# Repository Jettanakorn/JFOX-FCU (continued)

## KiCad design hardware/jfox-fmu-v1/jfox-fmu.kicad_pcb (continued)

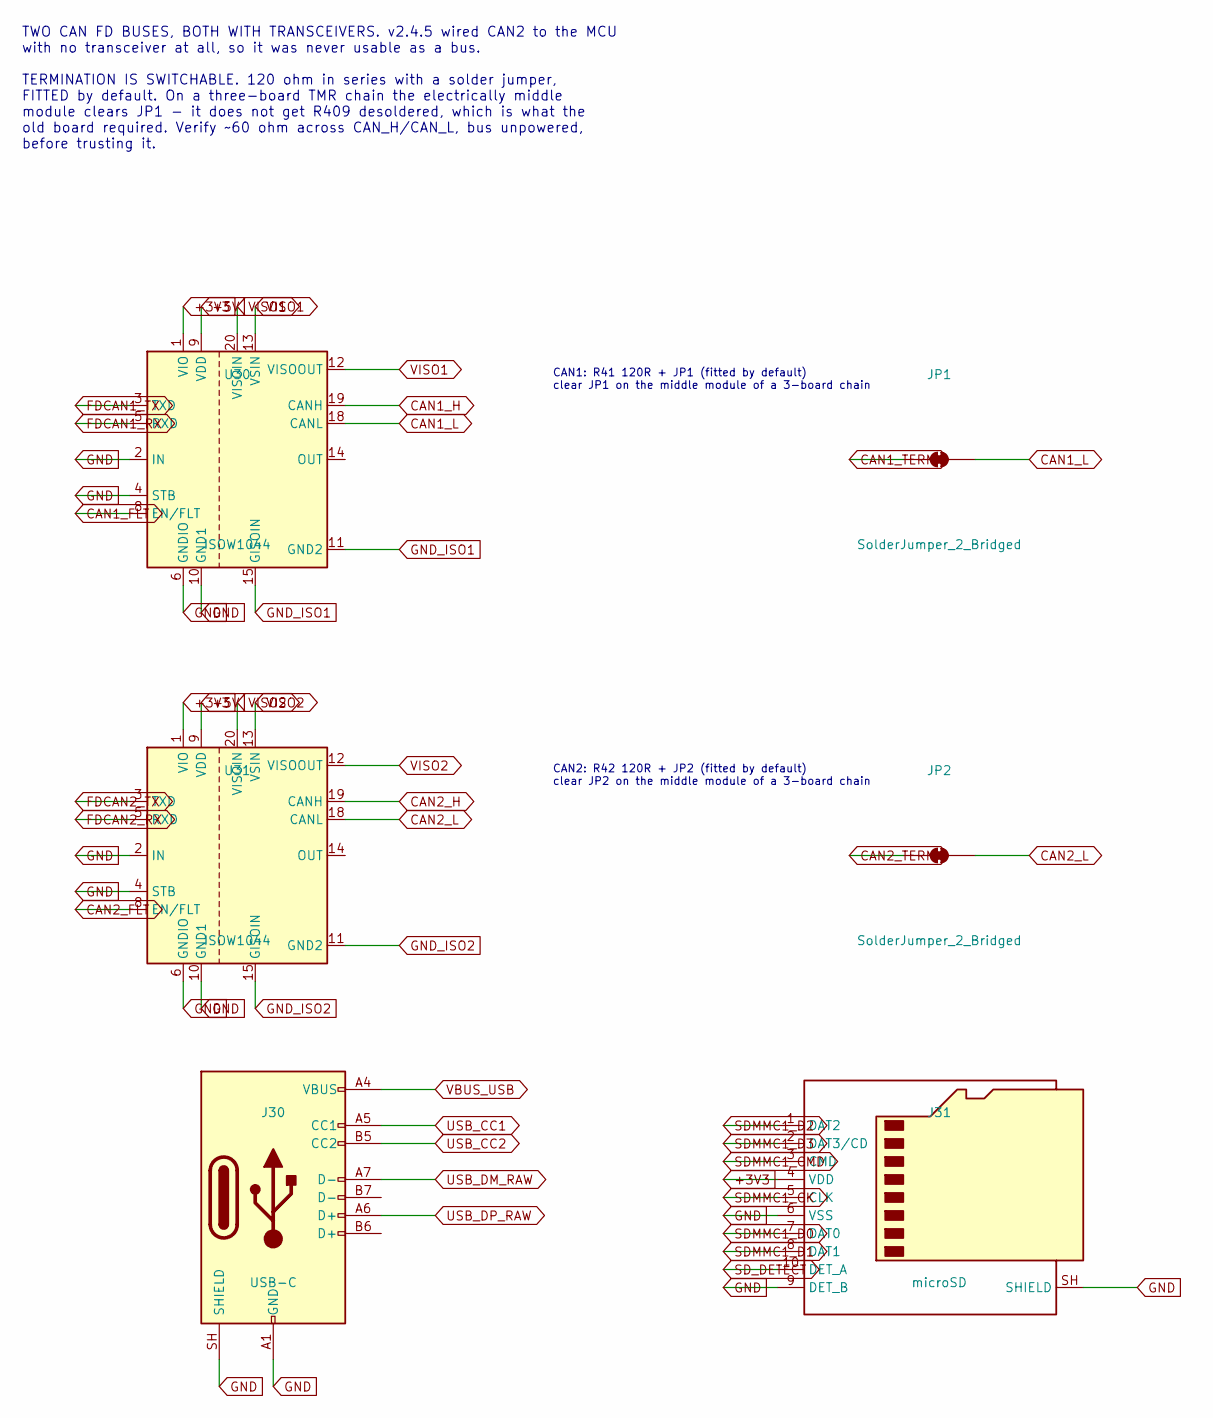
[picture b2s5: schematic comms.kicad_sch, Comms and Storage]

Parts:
J30: USB-C; USB_C_Receptacle_GCT_USB4085
J31: microSD; microSD_HC_Hirose_DM3AT-SF-PEJM5
JP1, JP2: SolderJumper_2_Bridged; SolderJumper-2_P1.3mm_Bridged_Pad1.0x1.5mm
U30, U31: ISOW1044; SOIC-20W_7.5x12.8mm_P1.27mm

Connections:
+3V3: J31.4 (VDD), U30.1 (VIO), U31.1 (VIO); also elsewhere on the board
+5V: U30.9 (VDD), U31.9 (VDD); also elsewhere on the board
CAN1_FLT: U30.8 (EN/FLT); also elsewhere on the board
CAN1_H: U30.19 (CANH); also elsewhere on the board
CAN1_L: JP1.2 (B), U30.18 (CANL); also elsewhere on the board
CAN1_TERM: JP1.1 (A); also elsewhere on the board
CAN2_FLT: U31.8 (EN/FLT); also elsewhere on the board
CAN2_H: U31.19 (CANH); also elsewhere on the board
CAN2_L: JP2.2 (B), U31.18 (CANL); also elsewhere on the board
CAN2_TERM: JP2.1 (A); also elsewhere on the board
FDCAN1_RX: U30.5 (RXD); also elsewhere on the board
FDCAN1_TX: U30.3 (TXD); also elsewhere on the board
FDCAN2_RX: U31.5 (RXD); also elsewhere on the board
FDCAN2_TX: U31.3 (TXD); also elsewhere on the board
GND: J30.A1 (GND), J30.A12 (GND), J30.B1 (GND), J30.B12 (GND), J30.SH (SHIELD), J31.6 (VSS), J31.9 (DET_B), J31.SH (SHIELD), U30.2 (IN), U30.4 (STB), U30.6 (GNDIO), U30.10 (GND1), U31.2 (IN), U31.4 (STB), U31.6 (GNDIO), U31.10 (GND1); also elsewhere on the board
GND_ISO1: U30.11 (GND2), U30.15 (GISOIN), U30.16 (GISOIN), U30.17 (GISOIN); also elsewhere on the board
GND_ISO2: U31.11 (GND2), U31.15 (GISOIN), U31.16 (GISOIN), U31.17 (GISOIN); also elsewhere on the board
SDMMC1_CK: J31.5 (CLK); also elsewhere on the board
SDMMC1_CMD: J31.3 (CMD); also elsewhere on the board
SDMMC1_D0: J31.7 (DAT0); also elsewhere on the board
SDMMC1_D1: J31.8 (DAT1); also elsewhere on the board
SDMMC1_D2: J31.1 (DAT2); also elsewhere on the board
SDMMC1_D3: J31.2 (DAT3/CD); also elsewhere on the board
SD_DETECT: J31.10 (DET_A); also elsewhere on the board
USB_CC1: J30.A5 (CC1); also elsewhere on the board
USB_CC2: J30.B5 (CC2); also elsewhere on the board
USB_DM_RAW: J30.A7 (D-); also elsewhere on the board
USB_DP_RAW: J30.A6 (D+); also elsewhere on the board
VBUS_USB: J30.A4 (VBUS), J30.A9 (VBUS), J30.B4 (VBUS), J30.B9 (VBUS); also elsewhere on the board
VISO1: U30.12 (VISOOUT), U30.13 (VSIN), U30.20 (VISOIN); also elsewhere on the board
VISO2: U31.12 (VISOOUT), U31.13 (VSIN), U31.20 (VISOIN); also elsewhere on the board

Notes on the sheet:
TWO CAN FD BUSES, BOTH WITH TRANSCEIVERS. v2.4.5 wired CAN2 to the MCU with no transceiver at all, so it was never usable as a bus. TERMINATION IS SWITCHABLE. 120 ohm in series with a solder jumper, FITTED by default. On a three-board TMR chain the electrically middle module clears JP1 - it does no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
CAN1: R41 120R + JP1 (fitted by default) clear JP1 on the middle module of a 3-board chain
CAN2: R42 120R + JP2 (fitted by default) clear JP2 on the middle module of a 3-board chain

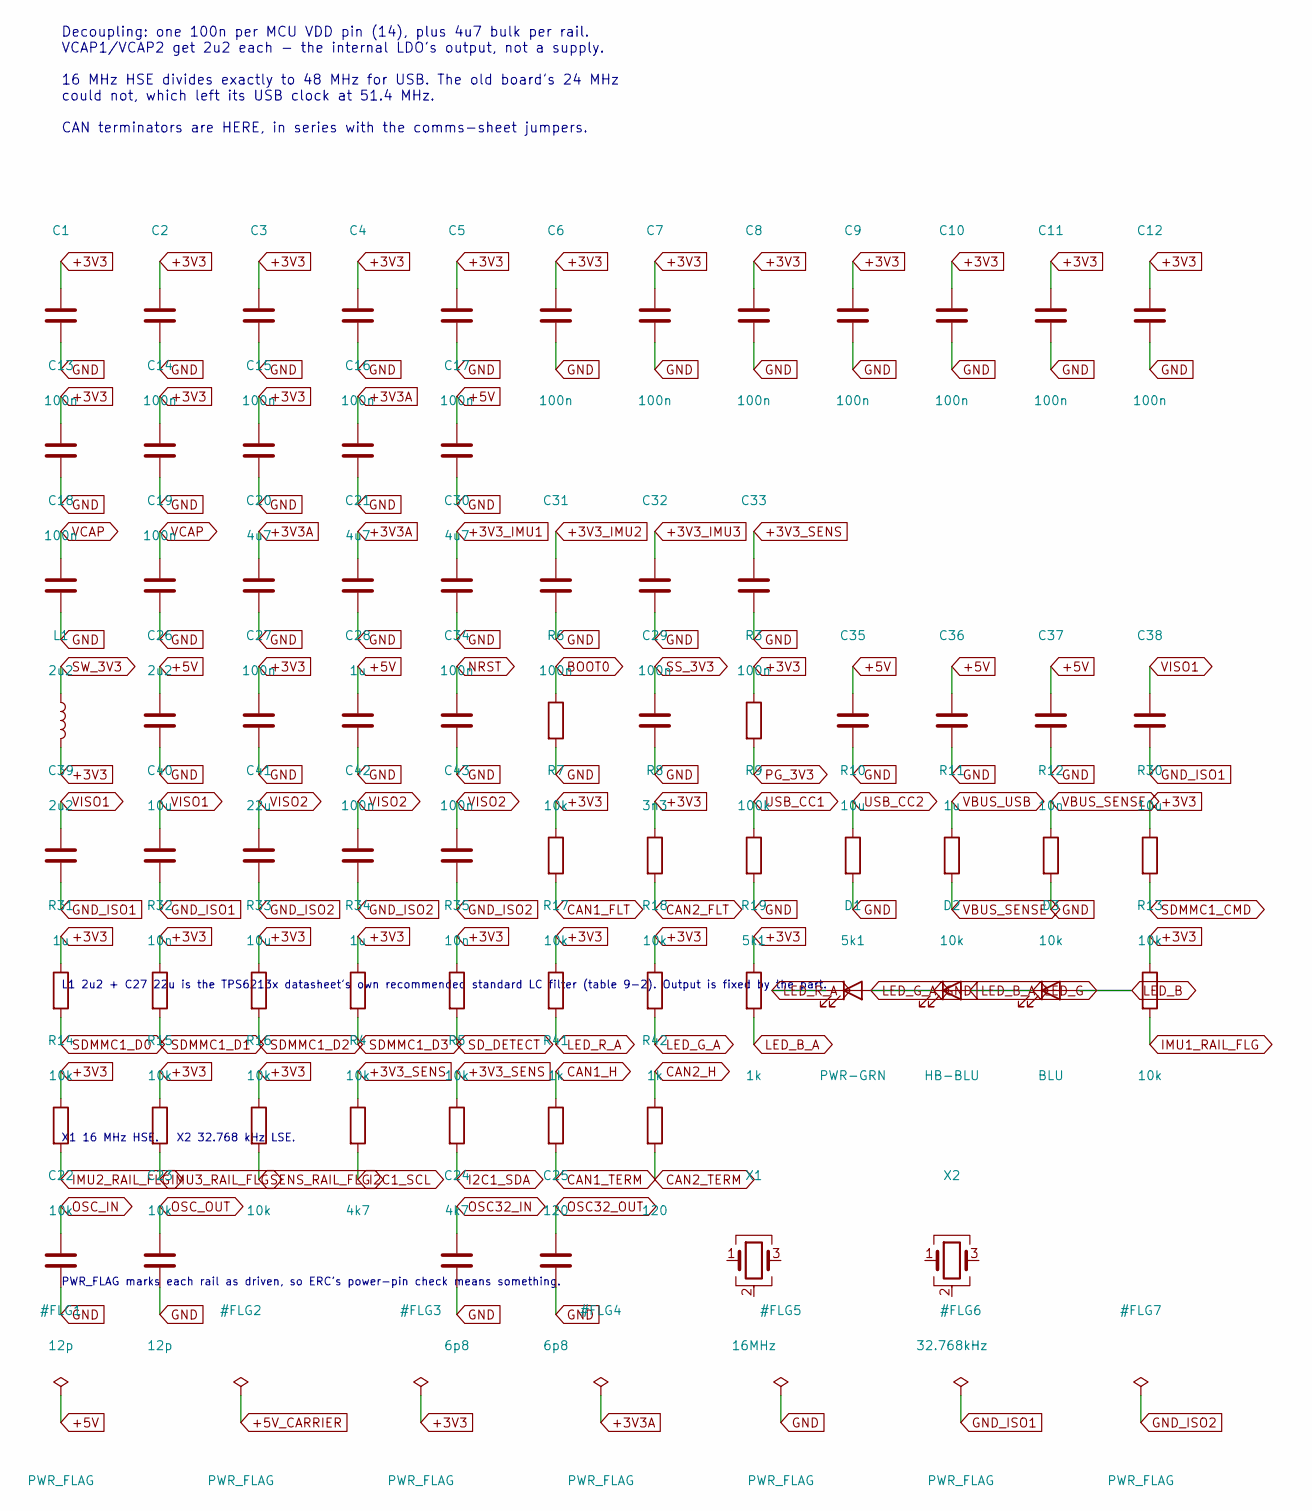
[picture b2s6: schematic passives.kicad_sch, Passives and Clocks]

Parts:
C1, C2, C3, C4, C5, C6, C7, C8, C9, C10, C11, C12, C13, C14, C20, C28, C30, C31, C32, C33, C34: 100n; C_0402_1005Metric
C15, C16, C17: 4u7; C_0805_2012Metric
C18, C19: 2u2; C_0402_1005Metric
C21, C36, C39, C42: 1u; C_0402_1005Metric
C22, C23: 12p; C_0402_1005Metric
C24, C25: 6p8; C_0402_1005Metric
C26, C35, C38, C41: 10u; C_0805_2012Metric
C27: 22u; C_0805_2012Metric
C29: 3n3; C_0402_1005Metric
C37, C40, C43: 10n; C_0402_1005Metric
D1: PWR-GRN; LED_0402_1005Metric
D2: HB-BLU; LED_0402_1005Metric
D3: BLU; LED_0402_1005Metric
L1: 2u2; L_1210_3225Metric
R3: 100k; R_0402_1005Metric
R4, R5: 4k7; R_0402_1005Metric
R6, R7, R8, R11, R12, R13, R14, R15, R16, R30, R31, R32, R33, R34, R35: 10k; R_0402_1005Metric
R9, R10: 5k1; R_0402_1005Metric
R17, R18, R19: 1k; R_0402_1005Metric
R41, R42: 120; R_0402_1005Metric
X1: 16MHz; Crystal_SMD_3225-4Pin_3.2x2.5mm
X2: 32.768kHz; Crystal_SMD_3225-4Pin_3.2x2.5mm

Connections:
+3V3: C1.1, C2.1, C3.1, C4.1, C5.1, C6.1, C7.1, C8.1, C9.1, C10.1, C11.1, C12.1, C13.1, C14.1, C15.1, C27.1, L1.2, R3.1, R7.1, R8.1, R13.1, R14.1, R15.1, R16.1, R17.1, R18.1, R19.1, R30.1, R31.1, R32.1, R33.1, R34.1, R35.1; also elsewhere on the board
+3V3A: C16.1, C20.1, C21.1; also elsewhere on the board
+3V3_IMU1: C30.1; also elsewhere on the board
+3V3_IMU2: C31.1; also elsewhere on the board
+3V3_IMU3: C32.1; also elsewhere on the board
+3V3_SENS: C33.1, R4.1, R5.1; also elsewhere on the board
+5V: C17.1, C26.1, C28.1, C35.1, C36.1, C37.1; also elsewhere on the board
BOOT0: R6.1; also elsewhere on the board
CAN1_FLT: R7.2; also elsewhere on the board
CAN1_H: R41.1; also elsewhere on the board
CAN1_TERM: R41.2; also elsewhere on the board
CAN2_FLT: R8.2; also elsewhere on the board
CAN2_H: R42.1; also elsewhere on the board
CAN2_TERM: R42.2; also elsewhere on the board
GND: C1.2, C2.2, C3.2, C4.2, C5.2, C6.2, C7.2, C8.2, C9.2, C10.2, C11.2, C12.2, C13.2, C14.2, C15.2, C16.2, C17.2, C18.2, C19.2, C20.2, C21.2, C22.2, C23.2, C24.2, C25.2, C26.2, C27.2, C28.2, C29.2, C30.2, C31.2, C32.2, C33.2, C34.2, C35.2, C36.2, C37.2, D1.2 (A), R6.2, R9.2, R10.2, R12.2; also elsewhere on the board
GND_ISO1: C38.2, C39.2, C40.2; also elsewhere on the board
GND_ISO2: C41.2, C42.2, C43.2; also elsewhere on the board
I2C1_SCL: R4.2; also elsewhere on the board
I2C1_SDA: R5.2; also elsewhere on the board
IMU1_RAIL_FLG: R13.2; also elsewhere on the board
IMU2_RAIL_FLG: R14.2; also elsewhere on the board
IMU3_RAIL_FLG: R15.2; also elsewhere on the board
LED_B: D3.2 (A); also elsewhere on the board
LED_B_A: D3.1 (K), R19.2
LED_G: D2.2 (A); also elsewhere on the board
LED_G_A: D2.1 (K), R18.2
LED_R_A: D1.1 (K), R17.2
NRST: C34.1; also elsewhere on the board
unnamed: X1.2 (G), X1.4 (G)
unnamed: X2.2 (G), X2.4 (G)
OSC32_IN: C24.1; also elsewhere on the board
OSC32_OUT: C25.1; also elsewhere on the board
OSC_IN: C22.1; also elsewhere on the board
OSC_OUT: C23.1; also elsewhere on the board
PG_3V3: R3.2; also elsewhere on the board
SDMMC1_CMD: R30.2; also elsewhere on the board
SDMMC1_D0: R31.2; also elsewhere on the board
SDMMC1_D1: R32.2; also elsewhere on the board
SDMMC1_D2: R33.2; also elsewhere on the board
SDMMC1_D3: R34.2; also elsewhere on the board
SD_DETECT: R35.2; also elsewhere on the board
SENS_RAIL_FLG: R16.2; also elsewhere on the board
SS_3V3: C29.1; also elsewhere on the board
SW_3V3: L1.1; also elsewhere on the board
USB_CC1: R9.1; also elsewhere on the board
USB_CC2: R10.1; also elsewhere on the board
VBUS_SENSE: R11.2, R12.1; also elsewhere on the board
VBUS_USB: R11.1; also elsewhere on the board
VCAP: C18.1, C19.1; also elsewhere on the board
VISO1: C38.1, C39.1, C40.1; also elsewhere on the board
VISO2: C41.1, C42.1, C43.1; also elsewhere on the board

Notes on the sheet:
Decoupling: one 100n per MCU VDD pin (14), plus 4u7 bulk per rail. VCAP1/VCAP2 get 2u2 each - the internal LDO's output, not a supply. 16 MHz HSE divides exactly to 48 MHz for USB. The old board's 24 MHz could not, which left its USB clock at 51.4 MHz. CAN terminators are HERE, in series with the c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
L1 2u2 + C27 22u is the TPS6213x datasheet's own recommended standard LC filter (table 9-2). Output is fixed by the part.
X1 16 MHz HSE. X2 32.768 kHz LSE.
PWR_FLAG marks each rail as driven, so ERC's power-pin check means something.

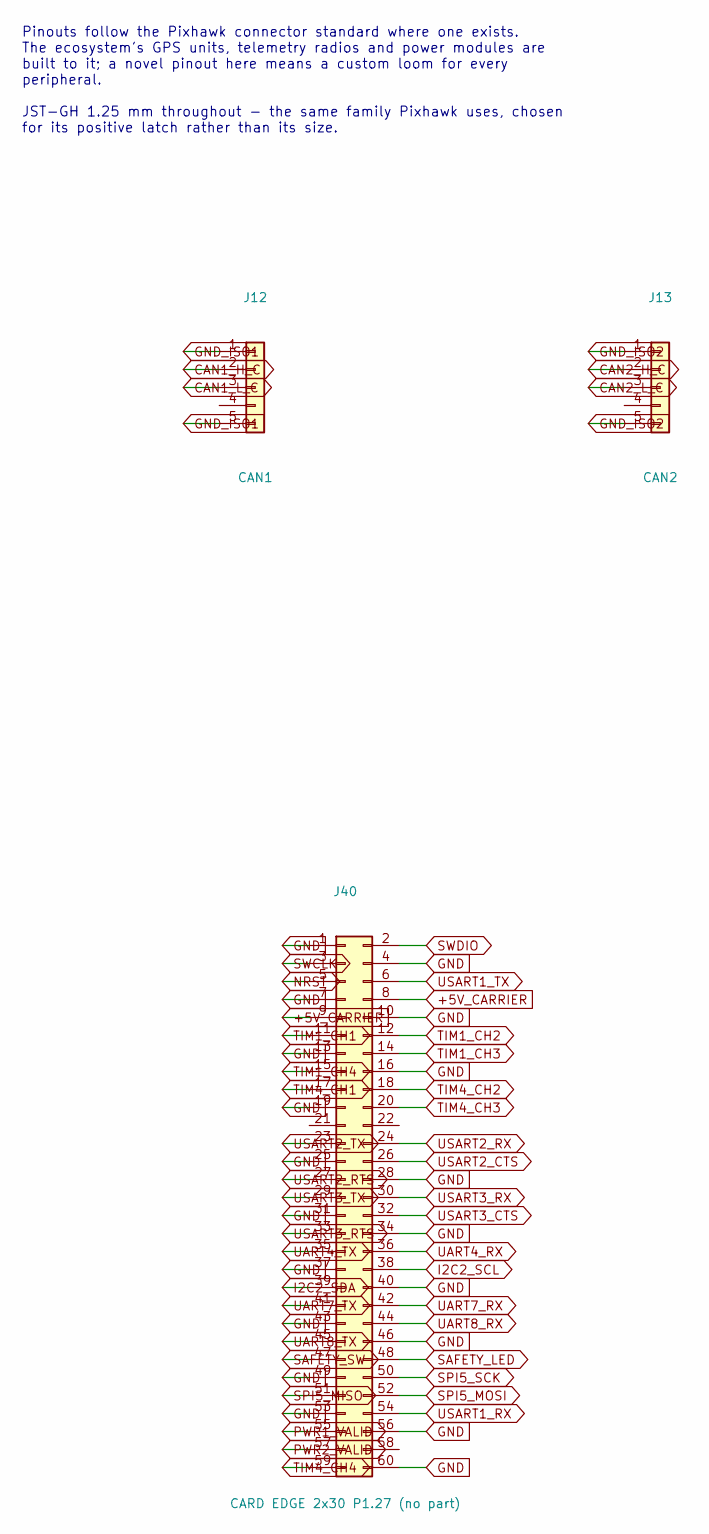
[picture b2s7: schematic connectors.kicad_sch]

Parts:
J12: CAN1; JST_GH_SM05B-GHS-TB_1x05-1MP_P1.25mm_Horizontal
J13: CAN2; JST_GH_SM05B-GHS-TB_1x05-1MP_P1.25mm_Horizontal
J40: CARD EDGE 2x30 P1.27 (no part); Samtec_MECF-30-0_-L-DV_2x30_P1.27mm_Polarized_Edge

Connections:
+5V_CARRIER: J40.8, J40.9; also elsewhere on the board
CAN1_H_C: J12.2; also elsewhere on the board
CAN1_L_C: J12.3; also elsewhere on the board
CAN2_H_C: J13.2; also elsewhere on the board
CAN2_L_C: J13.3; also elsewhere on the board
GND: J40.1, J40.4, J40.7, J40.10, J40.13, J40.16, J40.19, J40.25, J40.28, J40.31, J40.34, J40.37, J40.40, J40.43, J40.46, J40.49, J40.53, J40.56, J40.60; also elsewhere on the board
GND_ISO1: J12.1, J12.5; also elsewhere on the board
GND_ISO2: J13.1, J13.5; also elsewhere on the board
I2C2_SCL: J40.38; also elsewhere on the board
I2C2_SDA: J40.39; also elsewhere on the board
NRST: J40.5; also elsewhere on the board
PWR1_VALID: J40.55
PWR2_VALID: J40.57
SAFETY_LED: J40.48; also elsewhere on the board
SAFETY_SW: J40.47; also elsewhere on the board
SPI5_MISO: J40.51; also elsewhere on the board
SPI5_MOSI: J40.52; also elsewhere on the board
SPI5_SCK: J40.50; also elsewhere on the board
SWCLK: J40.3; also elsewhere on the board
SWDIO: J40.2; also elsewhere on the board
TIM1_CH1: J40.11; also elsewhere on the board
TIM1_CH2: J40.12; also elsewhere on the board
TIM1_CH3: J40.14; also elsewhere on the board
TIM1_CH4: J40.15; also elsewhere on the board
TIM4_CH1: J40.17; also elsewhere on the board
TIM4_CH2: J40.18; also elsewhere on the board
TIM4_CH3: J40.20; also elsewhere on the board
TIM4_CH4: J40.59; also elsewhere on the board
UART4_RX: J40.36; also elsewhere on the board
UART4_TX: J40.35; also elsewhere on the board
UART7_RX: J40.42; also elsewhere on the board
UART7_TX: J40.41; also elsewhere on the board
UART8_RX: J40.44; also elsewhere on the board
UART8_TX: J40.45; also elsewhere on the board
USART1_RX: J40.54; also elsewhere on the board
USART1_TX: J40.6; also elsewhere on the board
USART2_CTS: J40.26; also elsewhere on the board
USART2_RTS: J40.27; also elsewhere on the board
USART2_RX: J40.24; also elsewhere on the board
USART2_TX: J40.23; also elsewhere on the board
USART3_CTS: J40.32; also elsewhere on the board
USART3_RTS: J40.33; also elsewhere on the board
USART3_RX: J40.30; also elsewhere on the board
USART3_TX: J40.29; also elsewhere on the board

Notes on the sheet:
Pinouts follow the Pixhawk connector standard where one exists. The ecosystem's GPS units, telemetry radios and power modules are built to it; a novel pinout here means a custom loom for every peripheral. JST-GH 1.25 mm throughout - the same family Pixhawk uses, chosen for its positive latch rather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

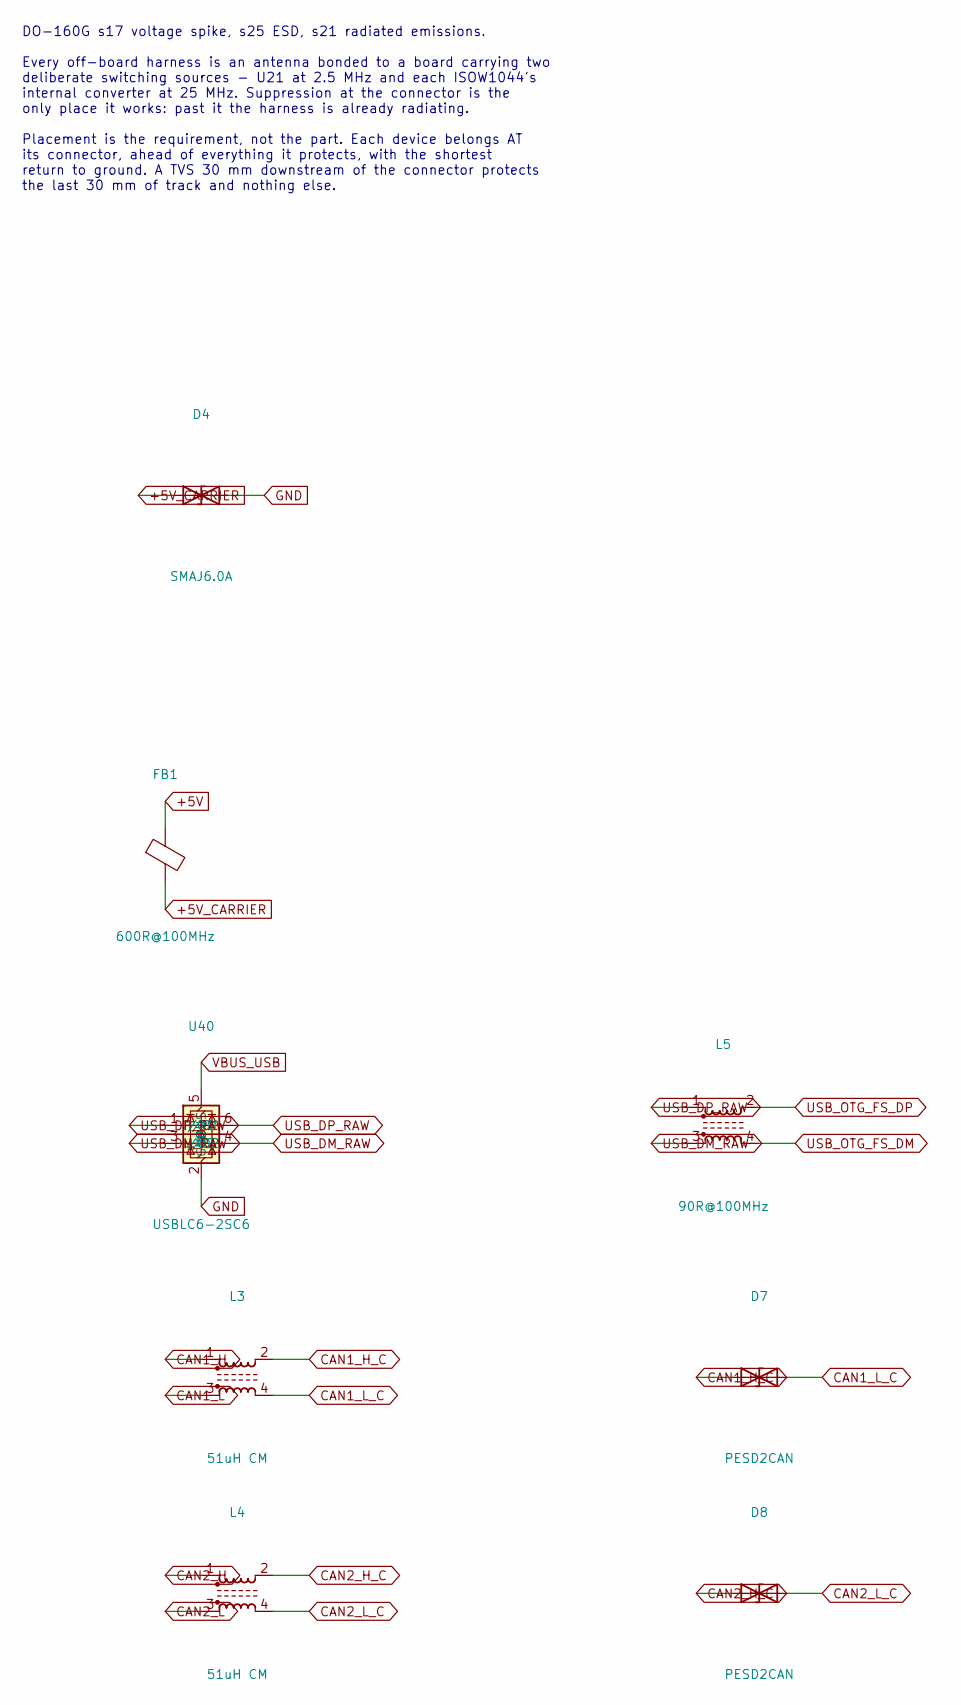
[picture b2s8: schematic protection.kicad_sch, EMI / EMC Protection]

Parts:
D4: SMAJ6.0A; D_SMA
D7, D8: PESD2CAN; D_SOD-323
FB1: 600R@100MHz; L_0805_2012Metric
L3, L4: 51uH CM; L_CommonModeChoke_Coilank_ACM1608
L5: 90R@100MHz; L_CommonModeChoke_Coilank_ACM1608
U40: USBLC6-2SC6; SOT-23-6

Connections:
+5V: FB1.1; also elsewhere on the board
+5V_CARRIER: D4.1 (A1), FB1.2; also elsewhere on the board
CAN1_H: L3.1; also elsewhere on the board
CAN1_H_C: D7.1 (A1), L3.2; also elsewhere on the board
CAN1_L: L3.3; also elsewhere on the board
CAN1_L_C: D7.2 (A2), L3.4; also elsewhere on the board
CAN2_H: L4.1; also elsewhere on the board
CAN2_H_C: D8.1 (A1), L4.2; also elsewhere on the board
CAN2_L: L4.3; also elsewhere on the board
CAN2_L_C: D8.2 (A2), L4.4; also elsewhere on the board
GND: D4.2 (A2), U40.2 (GND); also elsewhere on the board
USB_DM_RAW: L5.3, U40.3 (I/O2), U40.4 (I/O2); also elsewhere on the board
USB_DP_RAW: L5.1, U40.1 (I/O1), U40.6 (I/O1); also elsewhere on the board
USB_OTG_FS_DM: L5.4; also elsewhere on the board
USB_OTG_FS_DP: L5.2; also elsewhere on the board
VBUS_USB: U40.5 (VBUS); also elsewhere on the board

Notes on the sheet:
DO-160G s17 voltage spike, s25 ESD, s21 radiated emissions. Every off-board harness is an antenna bonded to a board carrying two deliberate switching sources - U21 at 2.5 MHz and each ISOW1044's internal converter at 25 MHz. Suppression at the connector is the only place it works: past it the harne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

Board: 6 copper layers, 105 parts (78 on the bottom side), 128 nets, no tracks yet.

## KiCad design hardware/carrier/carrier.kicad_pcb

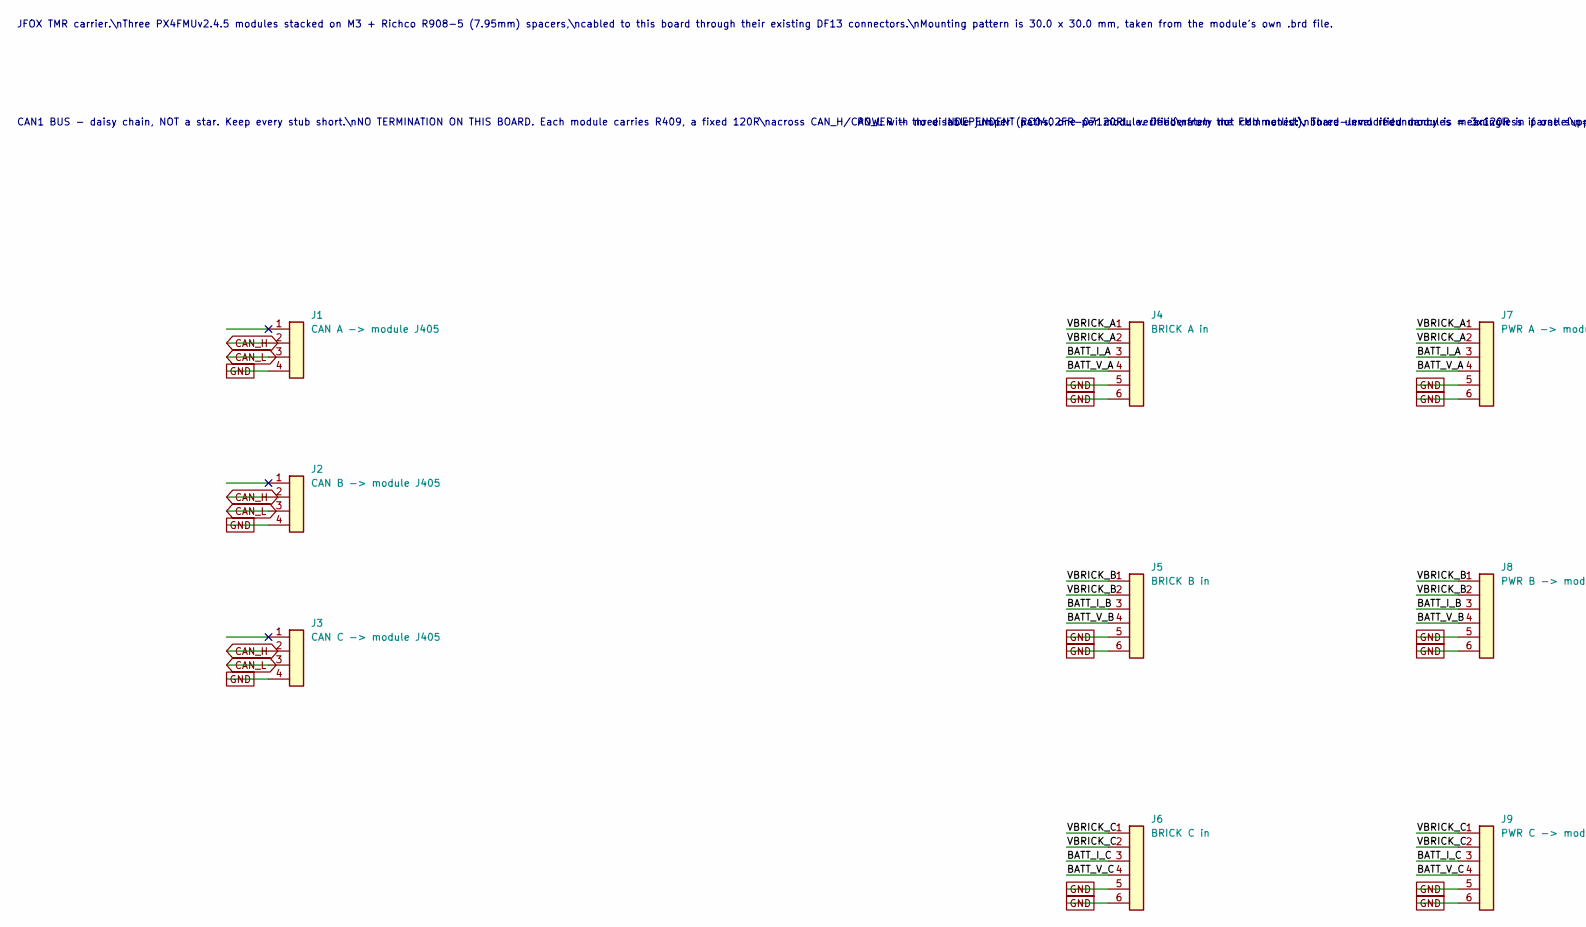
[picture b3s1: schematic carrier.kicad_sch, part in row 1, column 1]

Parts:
J1: CAN A -> module J405; Hirose_DF13-04P-1.25DSA_1x04_P1.25mm_Vertical
J2: CAN B -> module J405; Hirose_DF13-04P-1.25DSA_1x04_P1.25mm_Vertical
J3: CAN C -> module J405; Hirose_DF13-04P-1.25DSA_1x04_P1.25mm_Vertical
J4: BRICK A in; Hirose_DF13-06P-1.25DSA_1x06_P1.25mm_Vertical
J5: BRICK B in; Hirose_DF13-06P-1.25DSA_1x06_P1.25mm_Vertical
J6: BRICK C in; Hirose_DF13-06P-1.25DSA_1x06_P1.25mm_Vertical
J7: PWR A -> module J601; Hirose_DF13-06P-1.25DSA_1x06_P1.25mm_Vertical
J8: PWR B -> module J601; Hirose_DF13-06P-1.25DSA_1x06_P1.25mm_Vertical
J9: PWR C -> module J601; Hirose_DF13-06P-1.25DSA_1x06_P1.25mm_Vertical

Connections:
/BATT_I_A: J4.3, J7.3
/BATT_I_B: J5.3, J8.3
/BATT_I_C: J6.3, J9.3
/BATT_V_A: J4.4, J7.4
/BATT_V_B: J5.4, J8.4
/BATT_V_C: J6.4, J9.4
/VBRICK_A: J4.1, J4.2, J7.1, J7.2
/VBRICK_B: J5.1, J5.2, J8.1, J8.2
/VBRICK_C: J6.1, J6.2, J9.1, J9.2
CAN_H: J1.2, J2.2, J3.2
CAN_L: J1.3, J2.3, J3.3
GND: J1.4, J2.4, J3.4, J4.5, J4.6, J5.5, J5.6, J6.5, J6.6, J7.5, J7.6, J8.5, J8.6, J9.5, J9.6

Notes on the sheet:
JFOX TMR carrier.\nThree PX4FMUv2.4.5 modules stacked on M3 + Richco R908-5 (7.95mm) spacers,\ncabled to this board through their existing DF13 connectors.\nMounting pattern is 30.0 x 30.0 mm, taken from the module's own .brd file.
CAN1 BUS - daisy chain, NOT a star. Keep every stub short.\nNO TERMINATION ON THIS BOARD. Each module carries R409, a fixed 120R\nacross CAN_H/CAN_L with no disable jumper (RC0402FR-07120RL, verified\nfrom the FMU netlist). Three unmodified modules = 3x120R in parallel\n= ~40R, a real signal-integr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
POWER - three INDEPENDENT paths, one per module. Deliberately not commoned:\nboard-level redundancy is meaningless if one supply can take all three down.\nEach module still arbitrates its own inputs internally via LTC4417 (U1101).\nBrick in -> module out; the only shared net here is GND.

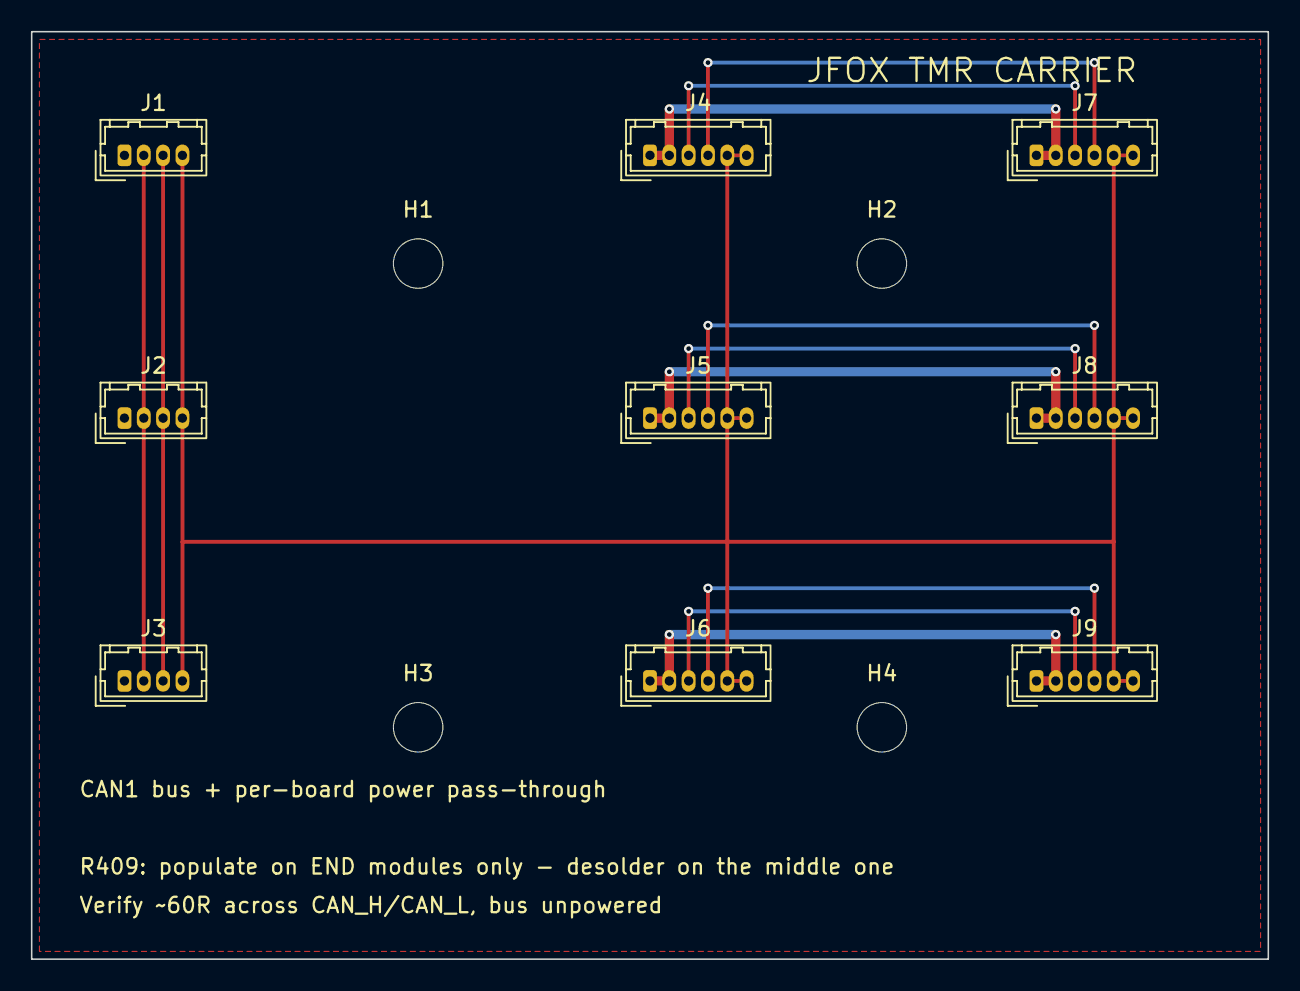
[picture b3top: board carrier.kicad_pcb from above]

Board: 2 copper layers, 80.0 x 60.0 mm, 13 parts (0 on the bottom side), 12 nets.

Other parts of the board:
H1, H2, H3, H4: MountingHole_3.2mm_M3

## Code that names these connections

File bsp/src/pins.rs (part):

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//! below) instead of the IO chip's 8, and there is no safety-switch/Spektrum/S.Bus input
//! available on this chip in this architecture.
//!
//! Prior versions of this file placed SPI1 on PE13/14/15 and SPI4 on PE12/13/14, which
//! directly collided with the PWM pins below and does not match the schematic; those
//! assignments have been corrected. AF (alternate function) numbers not explicitly
//! visible in the schematic text were carried over from the pre-existing convention
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pub struct PullDown;

// ==== SPI1 - MPU-6000 (Primary IMU) / internal sensor bus ("SPI_INT") ====
/// SPI1 SCK - PA5 (AF5)
pub type Spi1Sck = Pin<'A', 5, Alternate<5>>;
/// SPI1 MISO - PA6 (AF5)
pub type Spi1Miso = Pin<'A', 6, Alternate<5>>;
/// SPI1 MOSI - PA7 (AF5)
pub type Spi1Mosi = Pin<'A', 7, Alternate<5>>;
/// MPU-6000 Chip Select - PC2
pub type Mpu6000Cs = Pin<'C', 2, Output>;
/// MPU-6000 Data Ready - PD15
pub type Mpu6000Drdy = Pin<'D', 15, Input<PullUp>>;
/// Backup gyro (L3GD20) Chip Select - PC13, shares the SPI1/SPI_INT bus
pub type GyroCs = Pin<'C', 13, Output>;
/// Backup accel/mag (LSM303D) Chip Select - PC15, shares the SPI1/SPI_INT bus
pub type AccelMagCs = Pin<'C', 15, Output>;
/// Barometer (MS5611) Chip Select - PD7, shares the SPI1/SPI_INT bus
pub type BaroCs = Pin<'D', 7, Output>;

// ==== SPI2 - FRAM (FM25V01) ====
/// SPI2 SCK - PB13 (AF5)
pub type Spi2Sck = Pin<'B', 13, Alternate<5>>;
/// SPI2 MISO - PB14 (AF5)
pub type Spi2Miso = Pin<'B', 14, Alternate<5>>;
/// SPI2 MOSI - PB15 (AF5)
pub type Spi2Mosi = Pin<'B', 15, Alternate<5>>;
/// FRAM Chip Select - PD10
pub type FramCs = Pin<'D', 10, Output>;

// ==== SPI4 - External sensors ("SPI_EXT") ====
/// SPI4 SCK - PE2 (AF5)
pub type Spi4Sck = Pin<'E', 2, Alternate<5>>;
/// SPI4 NSS - PE4 (AF5)
pub type Spi4Nss = Pin<'E', 4, Alternate<5>>;
/// SPI4 MISO - PE5 (AF5)
pub type Spi4Miso = Pin<'E', 5, Alternate<5>>;
/// SPI4 MOSI - PE6 (AF5)
pub type Spi4Mosi = Pin<'E', 6, Alternate<5>>;

// ==== I2C1 - External sensors ====
/// I2C1 SCL - PB8 (AF4)
pub type I2c1Scl = Pin<'B', 8, Alternate<4>>;
/// I2C1 SDA - PB9 (AF4)
pub type I2c1Sda = Pin<'B', 9, Alternate<4>>;

// ==== I2C2 - LED driver (TCA62724) ====
/// I2C2 SCL - PB10 (AF4)
pub type I2c2Scl = Pin<'B', 10, Alternate<4>>;
/// I2C2 SDA - PB11 (AF4)
pub type I2c2Sda = Pin<'B', 11, Alternate<4>>;

// ==== UART1 (USART1) ====
/// UART1 TX - PA9 (AF7). Note: PA9 is also the VBUS-sense net on this board, and in the
/// dual-MCU reference design PA10 carries the IO-coprocessor debug console, not general
/// telemetry. Usable as a general-purpose UART in FMU-only builds; verify PA9 has no
/// conflicting analog load before relying on it.
pub type Uart1Tx = Pin<'A', 9, Alternate<7>>;
/// UART1 RX - PA10 (AF7)
pub type Uart1Rx = Pin<'A', 10, Alternate<7>>;

// ==== UART2 (USART2) ====
/// UART2 TX - PD5 (AF7)
pub type Uart2Tx = Pin<'D', 5, Alternate<7>>;
/// UART2 RX - PD6 (AF7)
pub type Uart2Rx = Pin<'D', 6, Alternate<7>>;
/// UART2 CTS - PD3 (AF7)
pub type Uart2Cts = Pin<'D', 3, Alternate<7>>;
/// UART2 RTS - PD4 (AF7)
pub type Uart2Rts = Pin<'D', 4, Alternate<7>>;

// ==== UART3 (USART3) - GPS ====
/// UART3 TX - PD8 (AF7)
pub type Uart3Tx = Pin<'D', 8, Alternate<7>>;
/// UART3 RX - PD9 (AF7)
pub type Uart3Rx = Pin<'D', 9, Alternate<7>>;
/// UART3 CTS - PD11 (AF7)
pub type Uart3Cts = Pin<'D', 11, Alternate<7>>;
/// UART3 RTS - PD12 (AF7)
pub type Uart3Rts = Pin<'D', 12, Alternate<7>>;

// ==== UART4 - GPS ====
/// UART4 TX - PA0 (AF8)
pub type Uart4Tx = Pin<'A', 0, Alternate<8>>;
/// UART4 RX - PA1 (AF8)
pub type Uart4Rx = Pin<'A', 1, Alternate<8>>;

// ==== UART7 ====
/// UART7 TX - PE8 (AF8)
pub type Uart7Tx = Pin<'E', 8, Alternate<8>>;
/// UART7 RX - PE7 (AF8)
pub type Uart7Rx = Pin<'E', 7, Alternate<8>>;

// ==== UART8 ====
/// UART8 TX - PE1 (AF8)
pub type Uart8Tx = Pin<'E', 1, Alternate<8>>;
/// UART8 RX - PE0 (AF8)
pub type Uart8Rx = Pin<'E', 0, Alternate<8>>;

// ==== FMU<->IO serial link (unused in FMU-only builds) ====
/// SERIAL_FMU_TO_IO - PC6. Free general-purpose pin when no IO co-processor is present.
pub type SerialFmuToIo = Pin<'C', 6, Alternate<7>>;
/// SERIAL_IO_TO_FMU - PC7. Free general-purpose pin when no IO co-processor is present.
pub type SerialIoToFmu = Pin<'C', 7, Alternate<7>>;

// ==== PWM Outputs - FMU-CH1..CH6 (TIM1/TIM4) ====
// Real PX4FMUv2.4.5 hardware only exposes 6 PWM channels directly on the FMU; the other
// 8 ("MAIN OUT") are generated by the separate IO co-processor this project doesn't
// implement (see module doc). PD12 and PD15 are NOT PWM pins on this chip (PD12 is
// Uart3Rts, PD15 is Mpu6000Drdy) - the previous 8-channel Pwm7/Pwm8 aliases on those
// pins have been removed.
/// PWM Channel 1 (FMU-CH1) - PE14 (TIM1_CH4, AF1)
pub type Pwm1 = Pin<'E', 14, Alternate<1>>;
/// PWM Channel 2 (FMU-CH2) - PE13 (TIM1_CH3, AF1)
pub type Pwm2 = Pin<'E', 13, Alternate<1>>;
/// PWM Channel 3 (FMU-CH3) - PE11 (TIM1_CH2, AF1)
pub type Pwm3 = Pin<'E', 11, Alternate<1>>;
/// PWM Channel 4 (FMU-CH4) - PE9 (TIM1_CH1, AF1)
pub type Pwm4 = Pin<'E', 9, Alternate<1>>;
/// PWM Channel 5 (FMU-CH5) - PD13 (TIM4_CH2, AF2)
pub type Pwm5 = Pin<'D', 13, Alternate<2>>;
/// PWM Channel 6 (FMU-CH6) - PD14 (TIM4_CH3, AF2)
pub type Pwm6 = Pin<'D', 14, Alternate<2>>;

// ==== CAN Bus ====
/// CAN1 TX - PD1 (AF9)
pub type Can1Tx = Pin<'D', 1, Alternate<9>>;
/// CAN1 RX - PD0 (AF9)
pub type Can1Rx = Pin<'D', 0, Alternate<9>>;
/// CAN2 TX - PB6 (AF9)
pub type Can2Tx = Pin<'B', 6, Alternate<9>>;
/// CAN2 RX - PB12 (AF9)
pub type Can2Rx = Pin<'B', 12, Alternate<9>>;

// ==== USB OTG FS ====
/// USB D- - PA11 (AF10)
pub type UsbDm = Pin<'A', 11, Alternate<10>>;
/// USB D+ - PA12 (AF10)
pub type UsbDp = Pin<'A', 12, Alternate<10>>;

// ==== Piezo Alarm ====
/// Alarm driver output - PA15 (TIM2_CH1)
pub type Alarm = Pin<'A', 15, Alternate<1>>;

// ==== Status LED (direct GPIO, in addition to the I2C2 TCA62724 RGB driver) ====
/// FMU amber LED - PE12. Direct GPIO, safe to use for e.g. a heartbeat/status indicator;
/// does not collide with any SPI/PWM/CAN pin above.
pub type FmuLedAmber = Pin<'E', 12, Output>;

// ==== ADC for Power/Sensor Sensing ====
/// Battery voltage sensing - PA2 (ADC1_IN2)
pub type VddSenseAdc = Pin<'A', 2, Analog>;
/// Battery current sensing - PA3 (ADC1_IN3)
pub type CurrentSenseAdc = Pin<'A', 3, Analog>;
/// 5V rail sensing - PA4 (ADC1_IN4)
pub type V5SenseAdc = Pin<'A', 4, Analog>;
/// Pressure sensor ADC - PC5 (analog baro option; PC1 is a separate spare ADC channel)
pub type PressureSenseAdc = Pin<'C', 5, Analog>;

// ==== Status LEDs (via TCA62724 I2C LED Driver on I2C2) ====
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}

// ==== Debug/SWD Interface ====
/// SWDIO - PA13
pub type Swdio = Pin<'A', 13, Alternate<0>>;
/// SWCLK - PA14
pub type Swclk = Pin<'A', 14, Alternate<0>>;

// ==== Boot Configuration ====
/// BOOT0 - Must be low for normal operation
/// BOOT1 - PB2 (fixed silicon function, independent of board net naming)
pub type Boot1 = Pin<'B', 2, Input>;

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
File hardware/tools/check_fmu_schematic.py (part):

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
# (net, ref, pin, why) - every one traceable to a datasheet table.
SIGNALS = [
    ("SPI2_MISO", "U1", "1",  "ICM-42688-P AP_SDO is pin 1 (DS-000347)"),
    ("SPI2_SCK",  "U1", "13", "ICM-42688-P AP_SCLK is pin 13"),
    ("SPI2_MOSI", "U1", "14", "ICM-42688-P AP_SDI is pin 14"),
    ("IMU2_CS",   "U1", "12", "ICM-42688-P AP_CS is pin 12"),
    ("IMU2_DRDY", "U1", "4",  "ICM-42688-P INT1 is pin 4"),
    ("SPI6_MISO", "U2", "1",  "ICM-45686 AP_SDO is pin 1 (DS-000577)"),
    ("IMU3_CS",   "U2", "12", "ICM-45686 AP_CS is pin 12"),
    ("I2C1_SCL",  "U4", "2",  "BMP388 SCK is pin 2 (BST-BMP388-DS001-07)"),
    ("I2C1_SDA",  "U4", "4",  "BMP388 SDI is pin 4"),
    ("BARO1_INT", "U4", "7",  "BMP388 INT is pin 7"),
    ("FRAM_CS",   "U5", "1",  "FM25V02A CS is pin 1 (001-90865)"),
    ("SPI4_MISO", "U5", "2",  "FM25V02A SO is pin 2"),
    ("SPI4_MOSI", "U5", "5",  "FM25V02A SI is pin 5"),
    ("SPI4_SCK",  "U5", "6",  "FM25V02A SCK is pin 6"),
]

# Ties the datasheets require, as opposed to merely permit.
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
    # Keyed by (ref, pin). Comparing bare reference designators gives false
    # alarms whenever one part sits on both nets - and U10 legitimately has
    # VCAP pins and VDD pins, so a ref-level comparison "proves" VCAP is
    # shorted to +3V3 on a perfectly good schematic. This is the second time
    # that mistake has been made here; compare pins, not parts.
    nets = {}
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def check_mcu(fails):
    """Every allocated signal must reach the pin the allocator chose.

    The netlist names pins by number; the allocation names them by port (PA9).
    The symbol carries both, so the mapping is read from it rather than
    assumed - and that is the whole point, since a schematic with SPI2_SCK on
    the wrong port pin is electrically valid and completely broken.
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
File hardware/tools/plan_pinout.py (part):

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    # --- sensor buses -----------------------------------------------------
    ("IMU1 BMI088",      "SPI1", ["SCK", "MISO", "MOSI"]),
    ("IMU2 ICM-42688-P", "SPI2", ["SCK", "MISO", "MOSI"]),
    # IMU3 is on SPI6, not SPI3: SPI3's only pins are PC10/11/12, which are
    # also SDMMC1's CK/D2/D3. Putting the third IMU there costs the SD card
    # its 4-bit mode. The allocator found this - it is not a guess.
    ("IMU3 ICM-45686",   "SPI6", ["SCK", "MISO", "MOSI"]),
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
# Pins that must stay free for their dedicated function.
RESERVED = {
    "PA13": "SWDIO (debug)",
    "PA14": "SWCLK (debug)",
    "PB3":  "SWO (trace)",
    "PC14": "OSC32_IN (LSE)",
    "PC15": "OSC32_OUT (LSE)",
    "PH0":  "OSC_IN (HSE 16 MHz)",
    "PH1":  "OSC_OUT (HSE 16 MHz)",
}


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
    This is a constraint problem, not a list to walk. Allocating in the order
    the wishlist happens to be written fails: SPI3 has many candidate pins and
    SDMMC1 has few, so taking SPI3 first can consume PC10/11/12 and leave
    SDMMC1 with nowhere to go - which is exactly what the first version did.

    So: pick the signal with the fewest remaining candidates each time
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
